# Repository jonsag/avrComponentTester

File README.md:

# avrComponentTester

Adapted from project at [https://www.mikrocontroller.net/articles/AVR_Transistortester](https://www.mikrocontroller.net/articles/AVR_Transistortester)

## Download repository

>$ git clone [https://github.com/jonsag/avrComponentTester.git](https://github.com/jonsag/avrComponentTester.git)

## Hardware

### Programmer

You will need an avr programmer like [this one](https://github.com/jonsag/USBaspProgrammer), or perhaps [this one](https://github.com/jonsag/ardAVRProgrammer).  

I'm using the first of these two.  
If you use an another programmer you will have to adapt the avrdude -c switch in the commands below, and change some lines in the Makefile.  

### Components tester

Look in directory  

    KiCAD/avrComponentTester

There you will find schematics and PCB layout.  

## Software

### Prerequisites

#### Install and prepare avrdude

>$ sudo apt install make binutils-avr avrdude avr-libc gcc-avr cross-avr-gcc9  
>
>$ usermod -a -G dialout,plugdev $USER  

You have to log out user to make new groups available.  

### ATmega328P with ST7735 1.8" OLED screen

#### Adapt software

In mega328_color_kit/Makefile, uncomment line to change direction of the rotary encoder  

    #CFLAGS += -DCHANGE_ROTARY_DIRECTION

->

    CFLAGS += -DCHANGE_ROTARY_DIRECTION

To use USBASP Programmer comment three lines  

    PROGRAMMER=avrispmkII
    BitClock=1.0
    PORT=usb

->

    PROGRAMMER=avrispmkII
    BitClock=1.0
    PORT=usb

and instead uncomment these three lines  

    #PROGRAMMER=usbasp
    #BitClock=20
    #PORT=usb

->

    PROGRAMMER=usbasp
    BitClock=20
    PORT=usb

In autoconf.h, modify two lines:  

    #define R_L_VAL 6800
    ...
    #define R_H_VAL 47000

Set values to match your resistors, ie:  

    #define R_L_VAL 6790
    ...
    #define R_H_VAL 46900

#### Tester software

>$ cd \<PATH_TO>/Software/ATmega328p_with_st7735/mega328_color_kit
>
>$ make upload

Write fuses  

>$ make fuses-crystal

Clean up  

>$ make clean

#### Alternative method

Compile software  

>$ make

This creates four new files:  

    mega328_color_kit.eep
    mega328_color_kit.hex
    mega328_color_kit.lss
    mega328_color_kit.map

and a directory with lots of files in:

    ../Obj/

Upload software and EEPROM

>$ avrdude -p m328p -P usb -c usbasp -B 20 -v -U flash:w:mega328_color_kit.hex -U eeprom:w:mega328_color_kit.eep

Set fuses  

>$ avrdude -p m328p -P usb -c usbasp -B 20 -v -U lfuse:w:0xF7:m -U hfuse:w:0xD9:m -U efuse:w:0xFC:m

Clean up  

>$ make clean

## Resources

### Fuse bits

Fuse bit calculator [here](https://www.engbedded.com/fusecalc/).  

Some reading [here](https://embedds.com/all-you-need-to-know-about-avr-fuses/).  

### avrdude

Some avrdude switches:

    -p partno; what type of part that is connected to the programmer
    -P port; port to identify the device to which the programmer is attached
    -c programmer-id; the programmer to be used
    -b baudrate; override the RS-232 connection baud rate
    -e ; causes a chip erase to be executed
    -F ; override device signature check
    -B bitclock; specify the bit clock period for the JTAG interface or the ISP clock
    -D ; disable auto erase for flash
    -v ; enable verbose output, more -v options increase verbosity level
    -U <memtype:op:filename[:format]>
        flash; the flash ROM of the device
            w; read the specified file and write it to the specified device memory
        lock; the lock byte
        efuse; the extended fuse byte
        hfuse; the high fuse byte
        lfuse; the low fuse byte
        boot; the boot flash area of ATxmega devices
    -t ; enter the interactive “terminal” mode

More on [this page](https://www.nongnu.org/avrdude/user-manual/avrdude_4.html).  

#### Erase avr flash memory

>$ avrdude -p m328p -P usb -c usbasp -B 20 -v -e

or  

>$ avrdude -p m328p -P usb -c usbasp -B 20 -v -t

    avrdude: AVR device initialized and ready to accept instructions

    Reading | ################################################## | 100% 0.08s

    avrdude: Device signature = 0x1e950f (probably m328p)
    avrdude> erase
    >>> erase 
    avrdude: erasing chip
    avrdude> quit
    >>> quit 

    avrdude: safemode: Fuses OK (E:FD, H:DF, L:FF)

    avrdude done.  Thank you.

#### Read from MCU to file

Read flash  

>$ avrdude -p m328p -P usb -c usbasp -B 20 -v -U flash:r:flash.hex:i  

Read EEPROM  

>$ avrdude -p m328p -P usb -c usbasp -B 20 -v -U eeprom:r:eeprom.eep:i  

Read fuse bits  

>$ avrdude -p m328p -P usb -c usbasp -B 20 -U lfuse:r:-:i -U hfuse:r:-:i -U efuse:r:-:i

#### Bootloader

Build bootloader  

>$ cd \<PATH_TO>/Bootloader/optiboot
>
>$ make atmega328p AVR_FREQ=8000000 BAUD_RATE=9600 LED_START_FLASHES=0 LED_DATA_FLASH=1

Now you got six new files:  

    baudcheck.tmp.sh
    optiboot_atmega328p.hex
    optiboot_atmega328p.log
    optiboot/optiboot_atmega328p.lst
    optiboot.elf
    optiboot.o

Burn bootloader  

>$ avrdude -p m328p -P usb -c usbasp -B 20 -v -U flash:w:optiboot_atmega328p.hex:i

Clean up  

>$ make clean

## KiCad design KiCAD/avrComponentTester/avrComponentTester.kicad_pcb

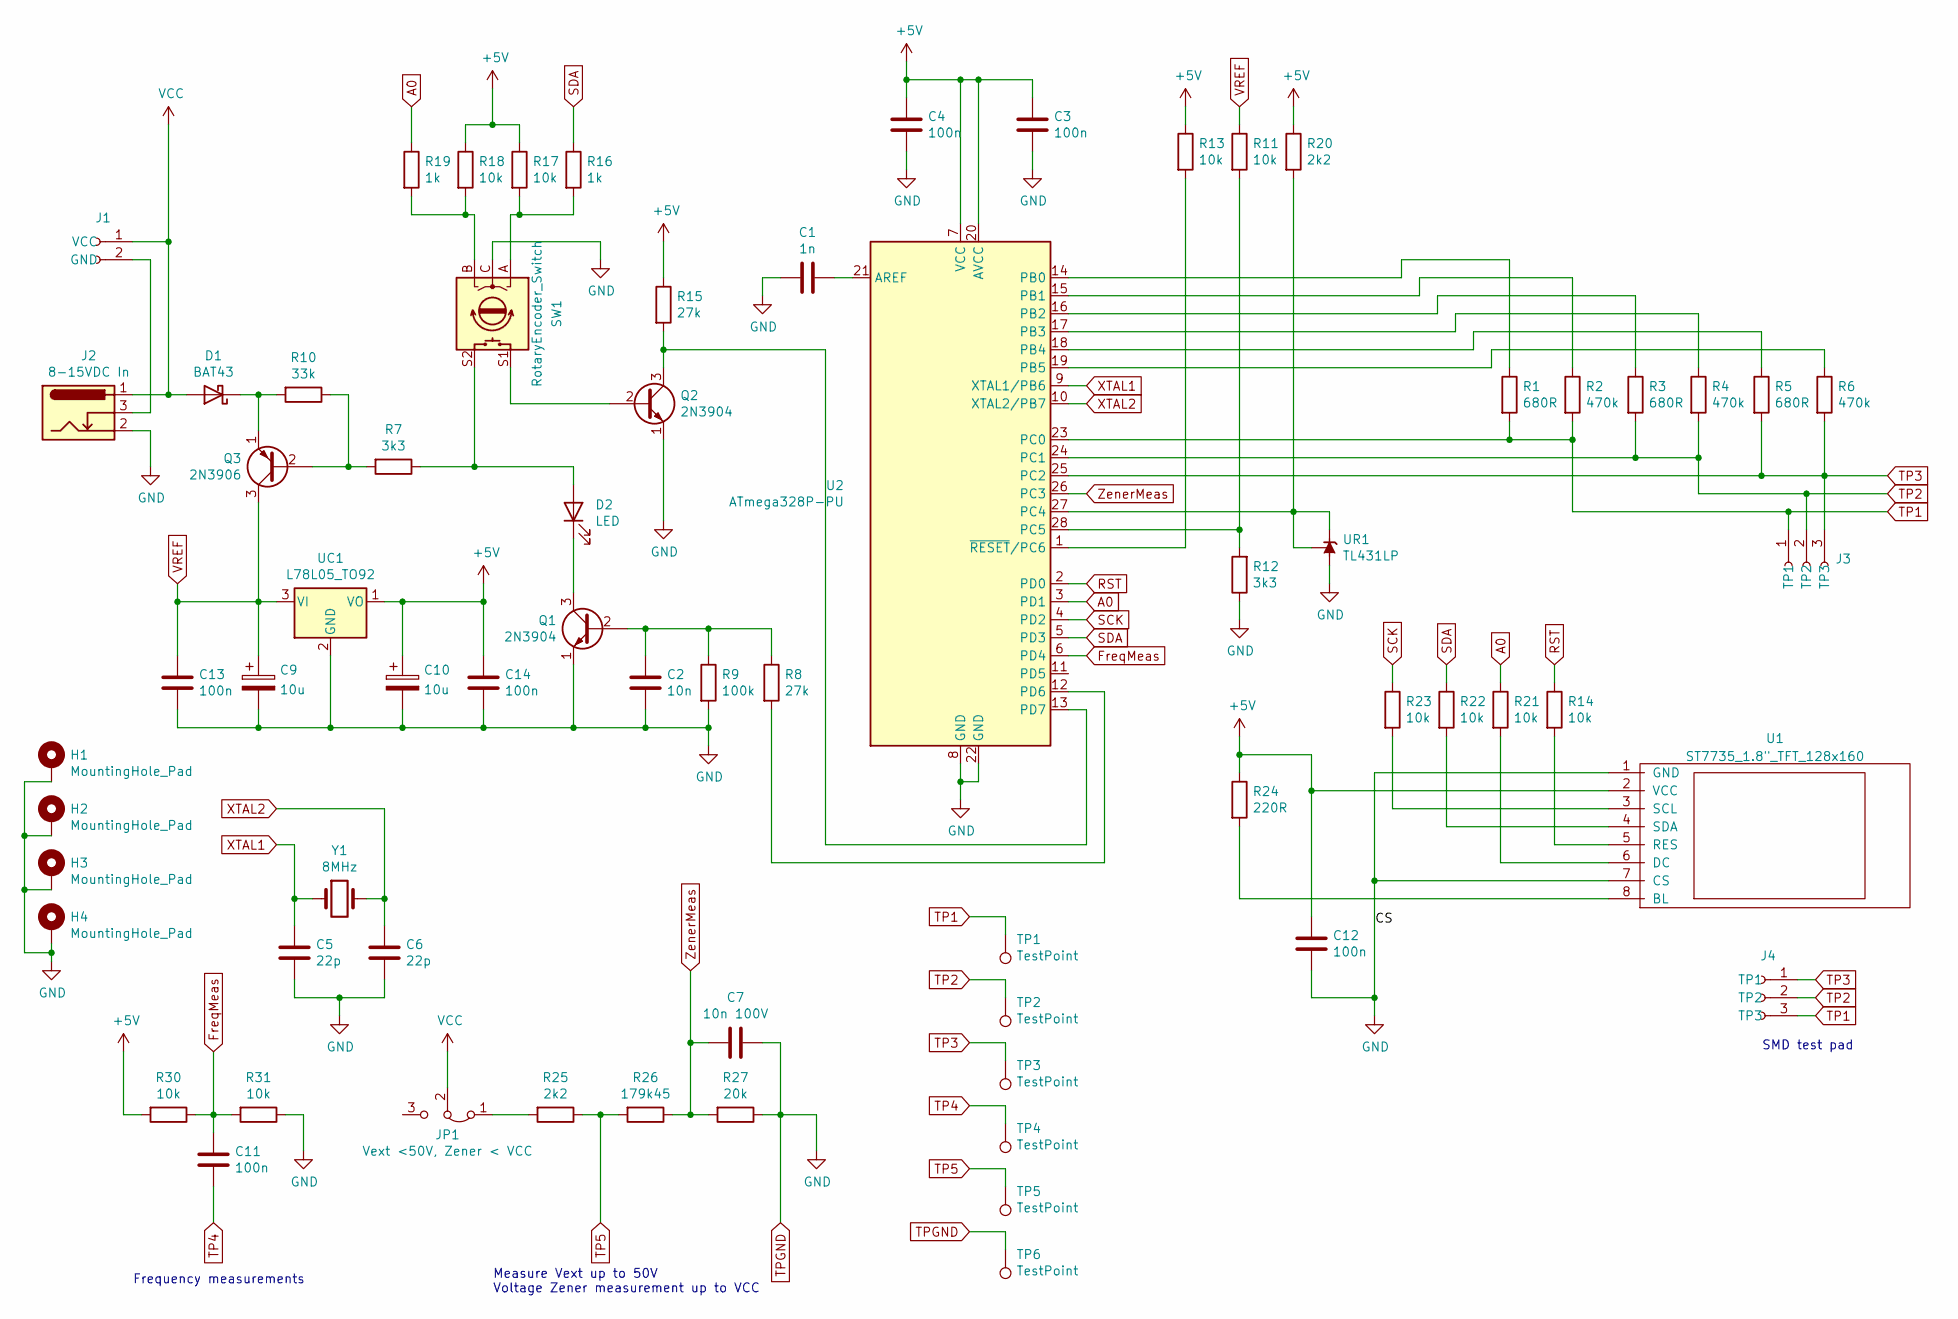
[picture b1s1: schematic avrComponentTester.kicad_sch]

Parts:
C1: 1n; C_Disc_D3.0mm_W1.6mm_P2.50mm_larg
C2: 10n; C_Disc_D3.8mm_W2.6mm_P2.50mm_large
C3, C4: 100n; C_Disc_D3.0mm_W1.6mm_P2.50mm_larg
C5, C6: 22p; C_Disc_D3.0mm_W1.6mm_P2.50mm_larg
C7: 10n 100V; C_Disc_D7.5mm_W2.5mm_P5.00mm_larger
C9, C10: 10u; CP_Radial_D5.0mm_P2.00mm_larger
C11, C12, C13, C14: 100n; C_Disc_D3.8mm_W2.6mm_P2.50mm_large
D1: BAT43; D_DO-35_SOD27_P7.62mm_Horizontal_large
D2: LED; LED_D5.0mm_larger_pads
H1, H2, H3, H4: MountingHole_Pad; MountingHole_3.2mm_M3_Pad
J1: 2-pin_power_input_header
J2: 8-15VDC In; BarrelJack_Horizontal
J3: 3-pin_test_header; 3-pin_test_header_large
J4: 3-pin_test_header; 3-pad_SMD_test-pad
JP1: Vext <50V, Zener < VCC; Jumper_1x03_P2.54mm_large
Q1, Q2: 2N3904; TO-92_Inline_Wide
Q3: 2N3906; TO-92_Inline_Wide
R1, R3, R5: 680R; R_Axial_DIN0207_L6.3mm_D2.5mm_P10.16mm_Horizontal_larger_pa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
R2, R4, R6: 470k; R_Axial_DIN0207_L6.3mm_D2.5mm_P10.16mm_Horizontal_larger_pa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
R7, R12: 3k3; R_Axial_DIN0207_L6.3mm_D2.5mm_P10.16mm_Horizontal_larger_pa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
R8, R15: 27k; R_Axial_DIN0207_L6.3mm_D2.5mm_P10.16mm_Horizontal_larger_pa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
R9: 100k; R_Axial_DIN0207_L6.3mm_D2.5mm_P10.16mm_Horizontal_larger_pa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
R10: 33k; R_Axial_DIN0207_L6.3mm_D2.5mm_P10.16mm_Horizontal_larger_pa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
R11, R13, R14, R17, R18, R21, R22, R23, R30, R31: 10k; R_Axial_DIN0207_L6.3mm_D2.5mm_P10.16mm_Horizontal_larger_pa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
R16, R19: 1k; R_Axial_DIN0207_L6.3mm_D2.5mm_P10.16mm_Horizontal_larger_pa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
R20, R25: 2k2; R_Axial_DIN0207_L6.3mm_D2.5mm_P10.16mm_Horizontal_larger_pa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
R24: 220R; R_Axial_DIN0207_L6.3mm_D2.5mm_P10.16mm_Horizontal_larger_pa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
R26: 179k45; R_Axial_DIN0207_L6.3mm_D2.5mm_P10.16mm_Horizontal_larger_pa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
R27: 20k; R_Axial_DIN0207_L6.3mm_D2.5mm_P10.16mm_Horizontal_larger_pa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
SW1: RotaryEncoder_Switch; RotaryEncoder_Alps_EC11E-Switch_Vertical_H20mm_large
TP1, TP2, TP3, TP4, TP5, TP6: TestPoint; TestPoint_THTPad_4.0x4.0mm_Drill3.0mm
U1: ST7735_1.8"_TFT_128x160; ST7735_1.8_TFT_display_128x160_large
U2: ATmega328P-PU; DIP-28_W7.62mm_LongPads w socket
UC1: L78L05_TO92; TO-92_Inline_Wide
UR1: TL431LP; TO-92_Inline_Wide
Y1: 8MHz; Crystal_HC49-4H_Vertical_large

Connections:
+5V: C3.1, C4.1, C10.1, C12.1, C14.1, R13.1, R15.1, R17.1, R18.1, R20.1, R24.1, R30.2, U1.2 (VCC), U2.7 (VCC), U2.20 (AVCC), UC1.1 (VO)
A0: R19.1, R21.1, U2.3 (PD1)
FreqMeas: C11.1, R30.1, R31.2, U2.6 (PD4)
unnamed: C1.1, U2.21 (AREF)
unnamed: C2.1, Q1.2 (B), R8.1, R9.1
unnamed: D1.1 (K), Q3.1 (E), R10.2
unnamed: D2.1 (K), Q1.3 (C)
unnamed: D2.2 (A), R7.1, SW1.S2
unnamed: J1.2 (GND), J2.3
unnamed: JP1.1 (A), R25.2
unnamed: Q2.2 (B), SW1.S1
unnamed: Q2.3 (C), R15.2, U2.13 (PD7)
unnamed: Q3.2 (B), R7.2, R10.1
unnamed: R1.1, U2.14 (PB0)
unnamed: R2.1, U2.15 (PB1)
unnamed: R3.1, U2.16 (PB2)
unnamed: R4.1, U2.17 (PB3)
unnamed: R5.1, U2.18 (PB4)
unnamed: R6.1, U2.19 (PB5)
unnamed: R8.2, U2.12 (PD6)
unnamed: R11.2, R12.2, U2.28 (PC5)
unnamed: R13.2, U2.1 (~RESET/PC6)
unnamed: R14.2, U1.5 (RES)
unnamed: R16.2, R17.2, SW1.A
unnamed: R18.2, R19.2, SW1.B
unnamed: R20.2, U2.27 (PC4), UR1.1 (REF), UR1.3 (K)
unnamed: R21.2, U1.6 (DC)
unnamed: R22.2, U1.4 (SDA)
unnamed: R23.2, U1.3 (SCL)
unnamed: R24.2, U1.8 (BL)
RST: R14.1, U2.2 (PD0)
SCK: R23.1, U2.4 (PD2)
SDA: R16.1, R22.1, U2.5 (PD3)
TP1: J3.1 (TP1), J4.3 (TP3), R1.2, R2.2, TP1.1, U2.23 (PC0)
TP2: J3.2 (TP2), J4.2 (TP2), R3.2, R4.2, TP2.1, U2.24 (PC1)
TP3: J3.3 (TP3), J4.1 (TP1), R5.2, R6.2, TP3.1, U2.25 (PC2)
TP4: C11.2, TP4.1
TP5: R25.1, R26.2, TP5.1
TPGND: C1.2, C2.2, C3.2, C4.2, C5.2, C6.2, C7.1, C9.2, C10.2, C12.2, C13.2, C14.2, H1.1, H2.1, H3.1, H4.1, J2.2, Q1.1 (E), Q2.1 (E), R9.2, R12.1, R27.1, R31.1, SW1.C, TP6.1, U1.1 (GND), U1.7 (CS), U2.8 (GND), U2.22 (GND), UC1.2 (GND), UR1.2 (A)
VCC: D1.2 (A), J1.1 (VCC), J2.1, JP1.2 (C)
VREF: C9.1, C13.1, Q3.3 (C), R11.1, UC1.3 (VI)
XTAL1: C5.1, U2.9 (XTAL1/PB6), Y1.1
XTAL2: C6.1, U2.10 (XTAL2/PB7), Y1.2
ZenerMeas: C7.2, R26.1, R27.2, U2.26 (PC3)

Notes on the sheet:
SMD test pad
Measure Vext up to 50V Voltage Zener measurement up to VCC
Frequency measurements

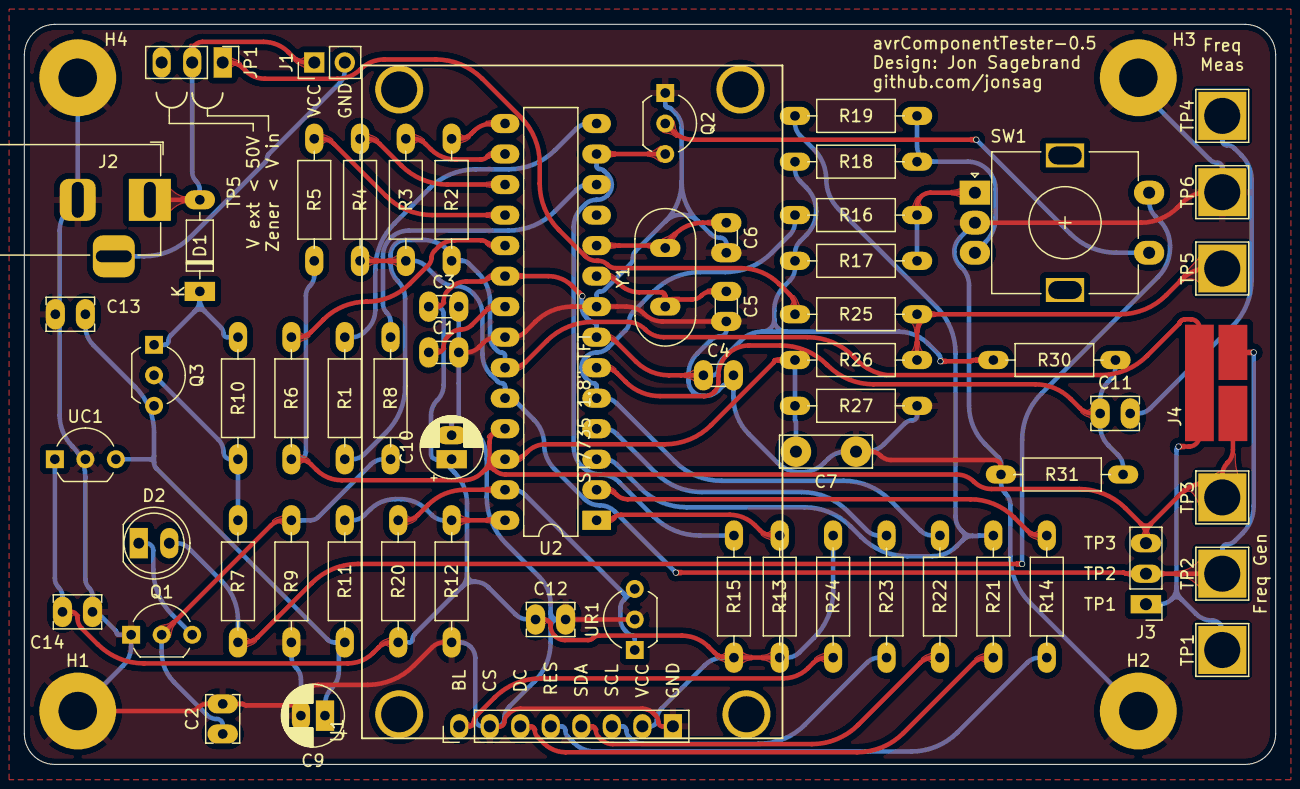
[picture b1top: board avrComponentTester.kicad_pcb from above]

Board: 2 copper layers, 104.1 x 61.6 mm, 68 parts (0 on the bottom side), 44 nets.

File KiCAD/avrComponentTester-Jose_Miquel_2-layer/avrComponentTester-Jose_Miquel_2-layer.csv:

Id;Designator;Package;Quantity;Designation;electrokit.se #
1;SW1;Rotary encoder with switch EC-11;1;EC11;
2;H4,H3,H2,H1;Mounting hole 3.2mm;4;MountingHole_Pad;
3;R22,R21,R31,R30,R23,R18,R17,R14,R13,R11;Resistor;10;10k;40810410
4;C14,C13,C4;Ceramic disc capacitor;3;100n;41003038
5;C1;Ceramic capacitor multilayer;1;1000p;41011994
6;J4;3-pad SMD test pad;1;3-pin_test_header;
7;U1;ST7735 1.8 OLED display with 8-pin female header;1;"ST7735_1.8""_TFT_128x160";
8;Y1;Crystal HC49-4H;1;8MHz;40420008
9;UR1;Precision references TO-92;1;TL431LP;40350431
10;UC1;Voltage regulator TO-92;1;L78L05;40350036
11;U2;Atmega328P-PU with DIP-28 socket;1;ATmega328P-PU;40360328
12;TP6,TP5,TP4,TP3,TP2,TP1;Test jack 2mm;6;TestPoint;41010335
13;R27;Resistor;1;20k;40811420
14;R26;Resistor;1;179k45;
15;R25,R20;Resistor;2;2k2;40810322
16;R24;Resistor;1;220R;40810222
17;R19,R16;Resistor;2;1k;40810310
18;R15,R8;Resistor;2;27k;40810427
19;R12,R7;Resistor;2;3k3;40810333
20;R10;Resistor;1;33k;40810433
21;R9;Resistor;1;100k;40810510
22;R6,R4,R2;Resistor 1%;3;470k;40810547
23;R5,R3,R1;Resistor 1%;3;680R;40810268
24;Q3;Bipolar junction transistor TO-92 PNP;1;2N3906;40320005
25;Q2,Q1;Bipolar junction transistor TO-92 NPN;2;2N3904;40320004
26;JP1;Three pin jumper;1;Vext <50V, Zener < VCC;41003010
27;J3;3-pin female header;1;3-pin_test_header;41003010
28;J2;DC barrel jack;1;8-15VDC In;41002169
29;D2;LED 5mm;1;LED;40307025
30;D1;Schottky diode DO-35 SOD27;1;BAT43;40310043
31;,C12,C11,C3;Ceramic capacitor multilayer;4;100n;41016717
32;C10,C9;Aluminium electrolytic capacitor;2;10u;40520003
33;C7;Mylar capacitor PC05;1;10n 100V;40510006
34;C6,C5;Ceramic disc capacitor;2;22p;40500116
35;C2;Ceramic capacitor multilayer;1;10n;41017770

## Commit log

2021-02-14 Software base
2021-02-14 Jose Miquel
2021-02-14 More CADs
2021-02-14 Correct software
2021-02-14 Cleaned
2021-02-14 Photos
2021-02-14 Moved stuff around
2021-02-14 a lot in README
2021-02-14 avrisp in Makefile
2021-02-15 README
2021-02-15 Makefile optimized
2021-02-15 KiCAD correction :-(
2021-02-15 New PCB and some READMEs
2021-02-16 READMEs
2021-02-17 now uploads with usbasp
2021-02-17 changed upload method to usbasp
2021-02-21 schematics
2021-02-23 kicad
2021-02-24 LTSpice
2021-03-17 my settings
2021-04-25 casing, gerber and pcb
2022-05-14 kicad6
2022-05-29 deletions and moving to new kicad dir
2022-09-09 kicad, readme
